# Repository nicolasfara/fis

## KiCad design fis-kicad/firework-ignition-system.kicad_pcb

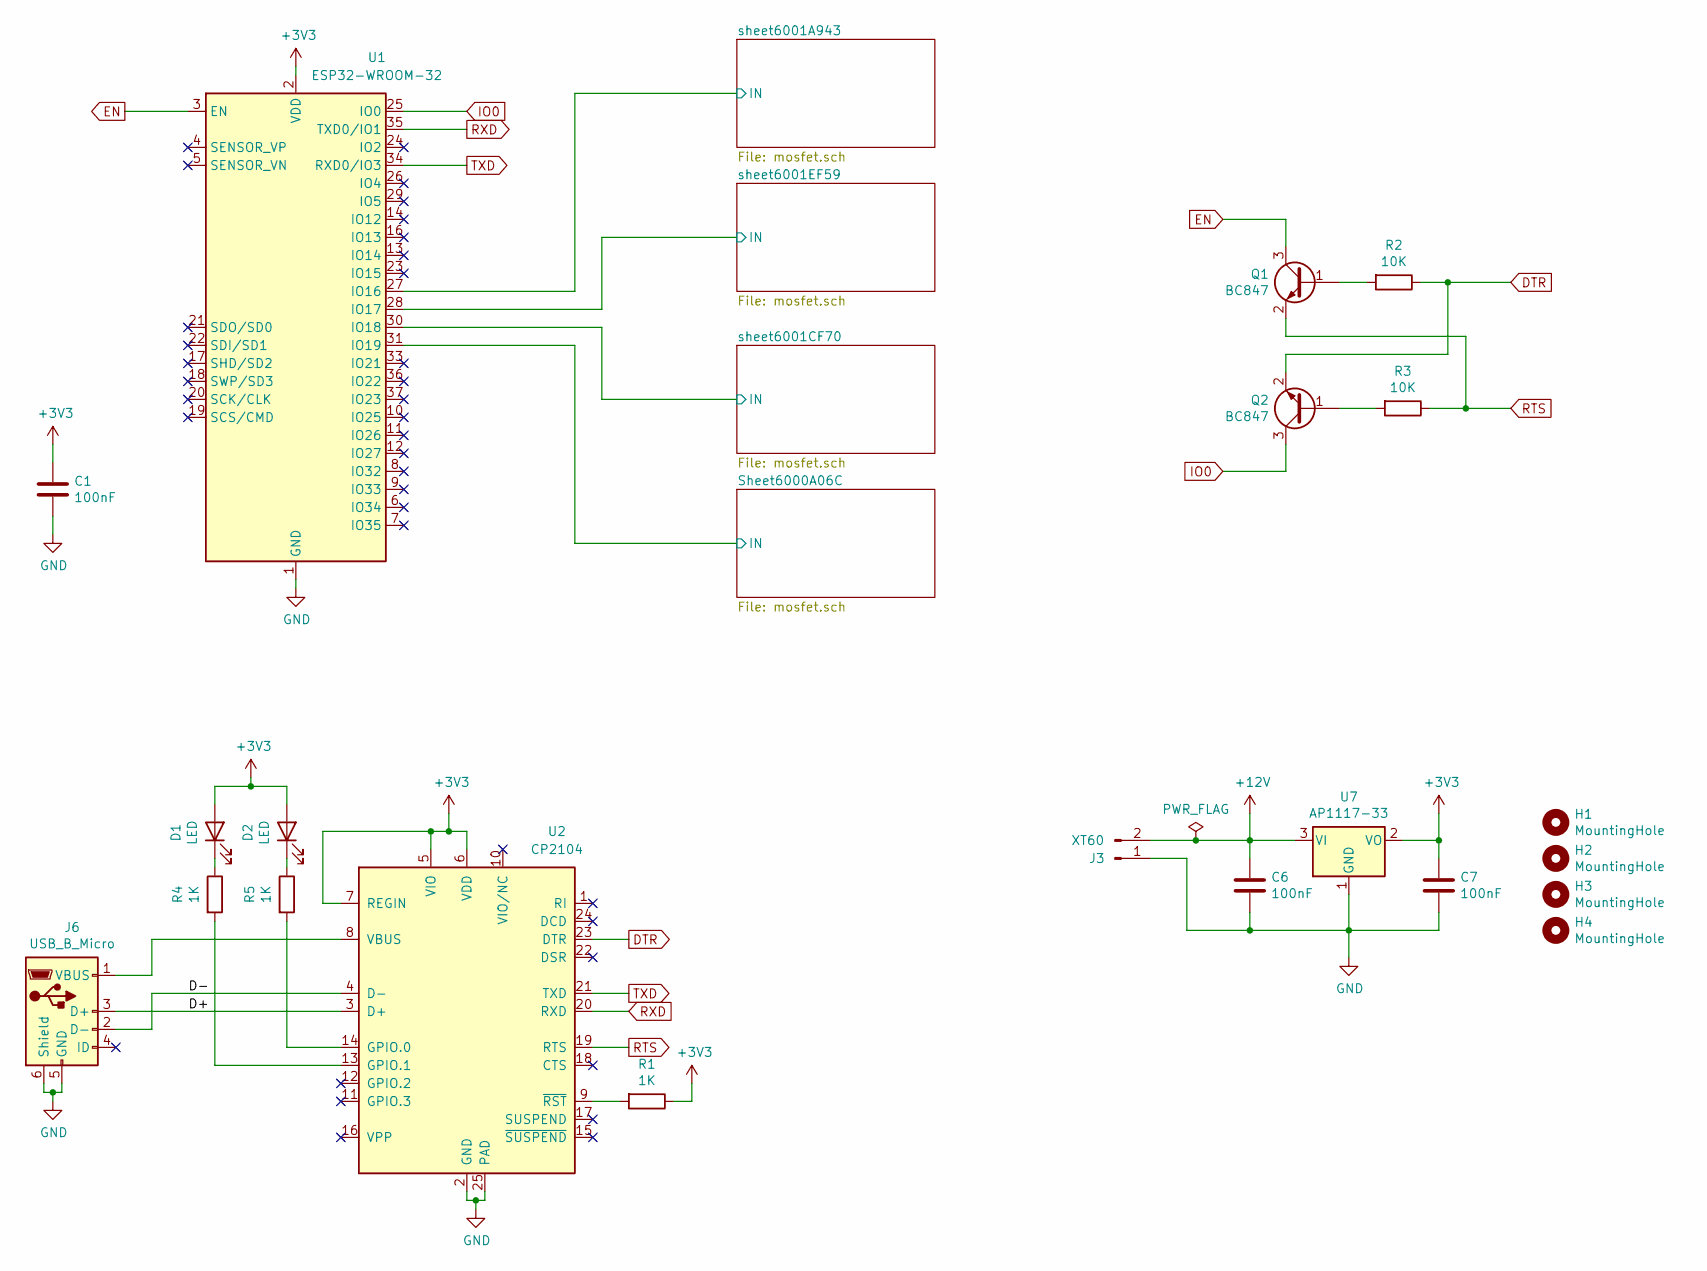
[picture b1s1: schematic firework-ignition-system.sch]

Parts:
C1, C6, C7: 100nF; C_1206_3216Metric; LCSC C24497
D1, D2: LED; LED_1206_3216Metric; LCSC C84270
H1, H2, H3, H4: MountingHole; MountingHole_3.2mm_M3
J3: XT60; AMASS_XT60-M_1x02_P7.20mm_Vertical
J6: USB_B_Micro; USB_Micro-B_Molex-105017-0001
Q1, Q2: BC847; SOT-23; LCSC C8664
R1, R4, R5: 1K; R_1206_3216Metric; LCSC C4410
R2, R3: 10K; R_1206_3216Metric; LCSC C17902
U1: ESP32-WROOM-32; LCSC C473012
U2: CP2104; QFN-24-1EP_4x4mm_P0.5mm_EP2.6x2.6mm; LCSC C47742
U7: AP1117-33; SOT-223-3_TabPin2; LCSC C108785

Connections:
+3V3: C1.1, C7.1, D1.2 (A), D2.2 (A), R1.1, U1.2 (VDD), U2.5 (VIO), U2.6 (VDD), U2.7 (REGIN), U7.2 (VO)
+12V: C6.1, J3.2, U7.3 (VI); also elsewhere on the board
/D+: J6.3 (D+), U2.3 (D+)
/D-: J6.2 (D-), U2.4 (D-)
/Sheet6000A06C/IN: U1.31 (IO19); also elsewhere on the board
/sheet6001A943/IN: U1.27 (IO16); also elsewhere on the board
/sheet6001CF70/IN: U1.30 (IO18); also elsewhere on the board
/sheet6001EF59/IN: U1.28 (IO17); also elsewhere on the board
DTR: Q2.2 (E), R2.1, U2.23 (DTR)
EN: Q1.3 (C), U1.3 (EN)
GND: C1.2, C6.2, C7.2, J3.1, J6.5 (GND), J6.6 (Shield), U1.1 (GND), U1.15 (GND), U1.38 (GND), U1.39 (GND), U2.2 (GND), U2.25 (PAD), U7.1 (GND); also elsewhere on the board
IO0: Q2.3 (C), U1.25 (IO0)
unnamed: D1.1 (K), R4.1
unnamed: D2.1 (K), R5.1
unnamed: J6.1 (VBUS), U2.8 (VBUS)
unnamed: Q1.1 (B), R2.2
unnamed: Q2.1 (B), R3.2
unnamed: R1.2, U2.9 (~RST)
unnamed: R4.2, U2.13 (GPIO.1)
unnamed: R5.2, U2.14 (GPIO.0)
RTS: Q1.2 (E), R3.1, U2.19 (RTS)
RXD: U1.35 (TXD0/IO1), U2.20 (RXD)
TXD: U1.34 (RXD0/IO3), U2.21 (TXD)

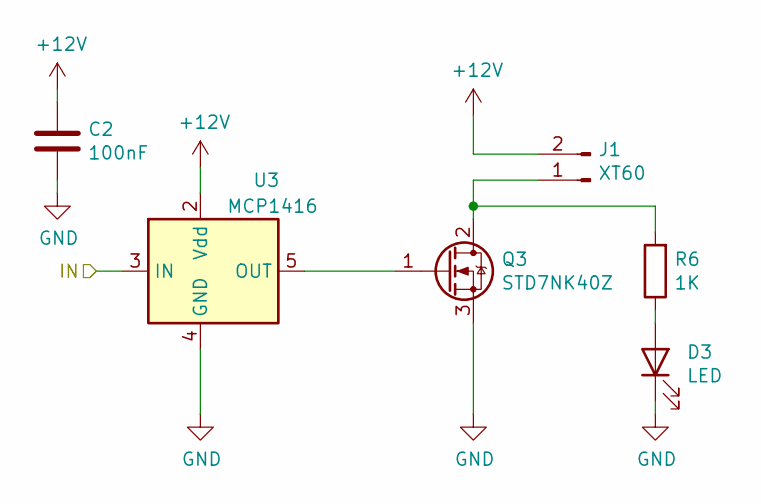
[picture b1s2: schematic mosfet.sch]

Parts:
C2: 100nF; C_1206_3216Metric; LCSC C24497
D3: LED; LED_D3.0mm
J1: XT60; AMASS_XT60-M_1x02_P7.20mm_Vertical
Q3: STD7NK40Z; TO-252-2; LCSC C500964
R6: 1K; R_1206_3216Metric; LCSC C4410
U3: MCP1416; SOT-23-5; LCSC C83775

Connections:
+12V: C2.1, J1.2, U3.2 (Vdd); also elsewhere on the board
/Sheet6000A06C/IN: U3.3 (IN); also elsewhere on the board
GND: C2.2, D3.1 (K), Q3.3 (S), U3.4 (GND); also elsewhere on the board
unnamed: D3.2 (A), R6.1
unnamed: J1.1, Q3.2 (D), R6.2
unnamed: Q3.1 (G), U3.5 (OUT)

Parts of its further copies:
C3, C4, C5: 100nF; C_1206_3216Metric; LCSC C24497
D4, D5, D6: LED; LED_D3.0mm
J2, J4, J5: XT60; AMASS_XT60-M_1x02_P7.20mm_Vertical
Q4, Q5, Q6: STD7NK40Z; TO-252-2; LCSC C500964
R7, R8, R9: 1K; R_1206_3216Metric; LCSC C4410
U4, U5, U6: MCP1416; SOT-23-5; LCSC C83775

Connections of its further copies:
+12V: C3.1, C4.1, C5.1, J2.2, J4.2, J5.2, U4.2 (Vdd), U5.2 (Vdd), U6.2 (Vdd); also elsewhere on the board
/sheet6001A943/IN: U4.3 (IN); also elsewhere on the board
/sheet6001CF70/IN: U5.3 (IN); also elsewhere on the board
/sheet6001EF59/IN: U6.3 (IN); also elsewhere on the board
GND: C3.2, C4.2, C5.2, D4.1 (K), D5.1 (K), D6.1 (K), Q4.3 (S), Q5.3 (S), Q6.3 (S), U4.4 (GND), U5.4 (GND), U6.4 (GND); also elsewhere on the board
unnamed: D4.2 (A), R7.1
unnamed: D5.2 (A), R8.1
unnamed: D6.2 (A), R9.1
unnamed: J2.1, Q4.2 (D), R7.2
unnamed: J4.1, Q5.2 (D), R8.2
unnamed: J5.1, Q6.2 (D), R9.2
unnamed: Q4.1 (G), U4.5 (OUT)
unnamed: Q5.1 (G), U5.5 (OUT)
unnamed: Q6.1 (G), U6.5 (OUT)

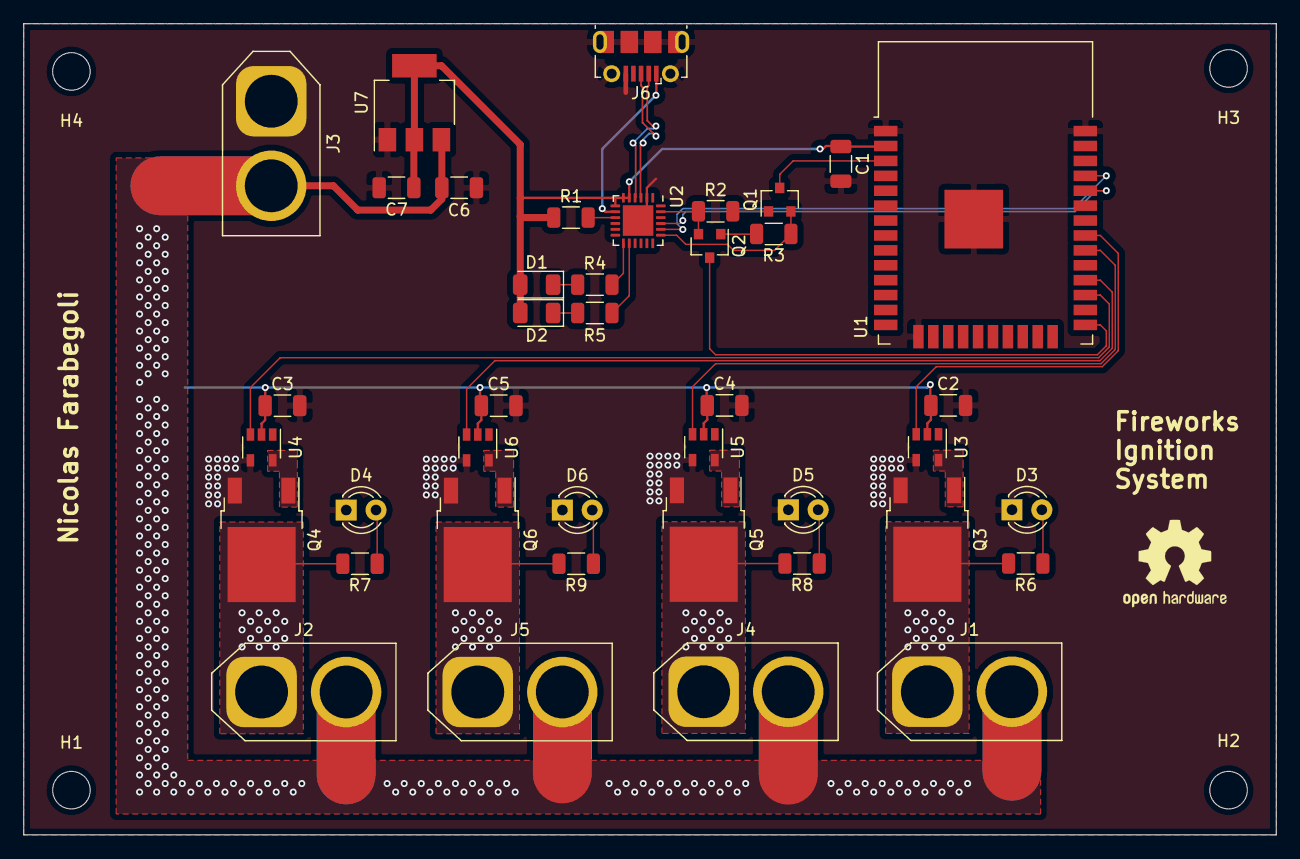
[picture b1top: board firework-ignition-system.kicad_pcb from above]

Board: 4 copper layers, 106.7 x 69.1 mm, 45 parts (0 on the bottom side), 35 nets.

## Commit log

2021-01-29 Add .gitignore
2021-01-29 Add code and schematics
2021-01-29 Add image to readme
2021-01-29 Add pdf schematic
2021-01-29 Add 3d case
2021-02-02 Add android to gitignore
2021-02-02 Add android app
2021-02-06 Finish android app
